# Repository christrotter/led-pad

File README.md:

# led-pad

NOTE: v2.0 is currently un-tested, but the order is on the way.

A simple PCB featuring a light-touch five-way switch with four leds, connecting via 12-pin 0.5mm-pitch FFC.
These are used as the dpad on my keyboards.

The SKRHACE010 five-way switch was used on my other pcb, and it's quite nice to use.  The [datasheet](https://www.mouser.ca/datasheet/2/15/SKRH-1370966.pdf) says it's 120gf operating force, but in practice it feels much lighter, especially compared to the Omron B3U-1000P (150gb +/-50gf).

The only challenge is the stem size is very small (1.95mm square).

I added the SK6805-EC15 LEDs at each direction because more visible is more better.

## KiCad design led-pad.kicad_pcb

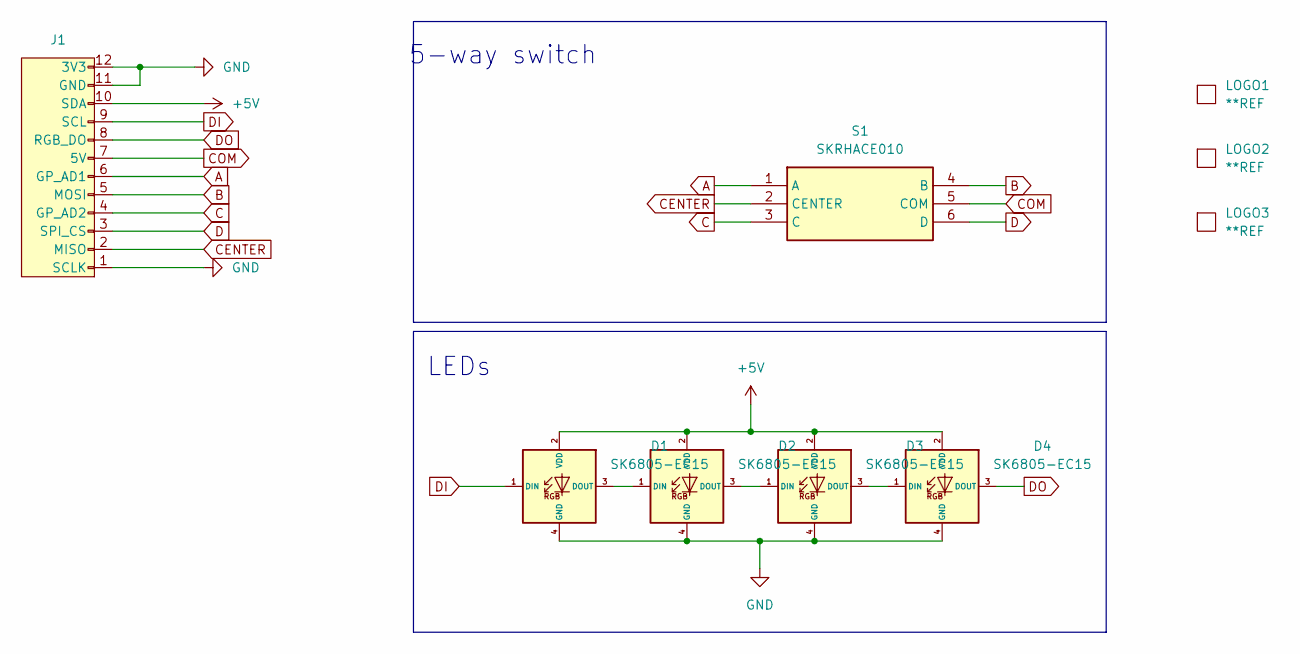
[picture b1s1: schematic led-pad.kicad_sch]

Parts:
D1, D2, D3, D4: SK6805-EC15; LED_dilemma_SK6805-EC15_1.5x1.5mm_P0.6mm_handsolder; MPN SK6805-EC15; LCSC C2890035
J1: vik-module-connector; FFC-SMD_FFC05001-12SBA124W5M
LOGO1, LOGO2: **REF; awesome-logo
LOGO3: **REF; led-pad-qr-10mm
S1: SKRHACE010; SW-SMD_SKRHACE010; Manufacturer_Part_Number SKRHACE010; Mouser Part Number 688-SKRHAC

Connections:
+5V: D1.2 (VDD), D2.2 (VDD), D3.2 (VDD), D4.2 (VDD), J1.10 (SDA)
A: J1.6 (GP_AD1), S1.1 (A)
B: J1.5 (MOSI), S1.4 (B)
C: J1.4 (GP_AD2), S1.3 (C)
CENTER: J1.2 (MISO), S1.2 (CENTER)
COM: J1.7 (5V), S1.5 (COM)
D: J1.3 (SPI_CS), S1.6 (D)
DI: D1.1 (DIN), J1.9 (SCL)
DO: D4.3 (DOUT), J1.8 (RGB_DO)
GND: D1.4 (GND), D2.4 (GND), D3.4 (GND), D4.4 (GND), J1.1 (SCLK), J1.11 (GND), J1.12 (3V3)
unnamed: D1.3 (DOUT), D2.1 (DIN)
unnamed: D2.3 (DOUT), D3.1 (DIN)
unnamed: D3.3 (DOUT), D4.1 (DIN)

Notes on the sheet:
5-way switch
LEDs

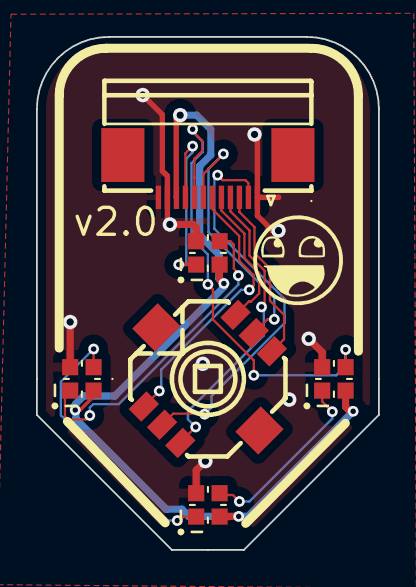
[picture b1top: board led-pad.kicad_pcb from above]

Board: 2 copper layers, 19.0 x 28.5 mm, 9 parts (2 on the bottom side), 13 nets.

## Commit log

2024-04-30 adding readme and images
2024-04-30 adding kicad files
2025-08-30 reworking for ffc connector, adding step file
2025-08-30 updating readme
